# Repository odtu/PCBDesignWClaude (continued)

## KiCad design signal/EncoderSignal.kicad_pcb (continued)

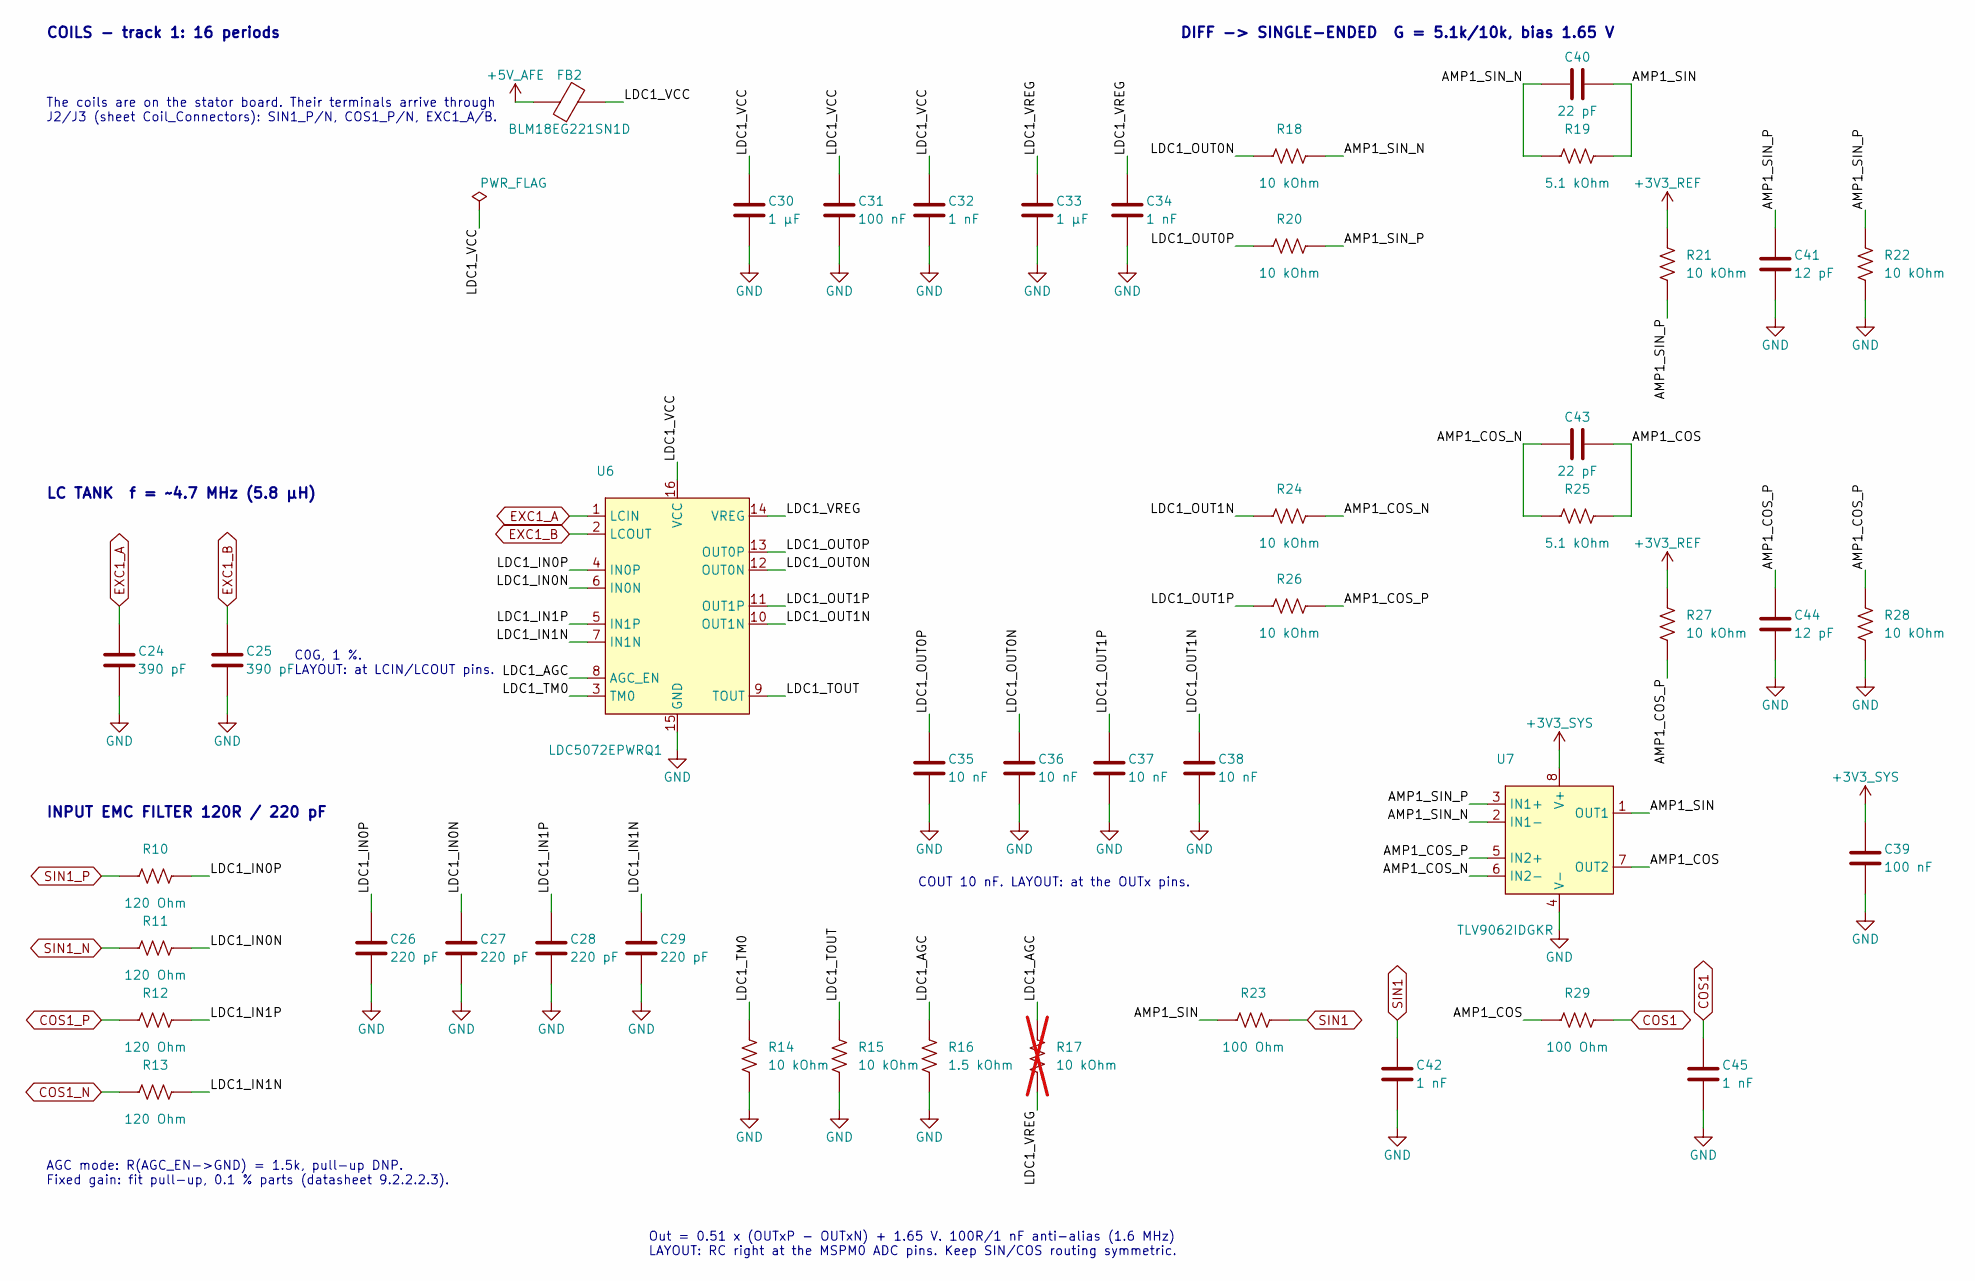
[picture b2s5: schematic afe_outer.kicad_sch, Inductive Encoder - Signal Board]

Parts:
C24, C25: 390 pF; 0603_Medium; Tolerance ±5%; Voltage Rating 50V; Digi-Key Number 490-8006-1-ND
C26, C27, C28, C29: 220 pF; 0603_Medium; Tolerance ±5%; Voltage Rating 50V; Digi-Key Number 1276-1985-1-ND
C30, C33: 1 µF; 0603_Medium; Tolerance ±10%; Voltage Rating 10V; Digi-Key Number 1276-1946-1-ND
C31, C39: 100 nF; 0603_Medium; Tolerance ±10%; Voltage Rating 16V; Digi-Key Number 311-1088-1-ND
C32, C34, C42, C45: 1 nF; 0603_Medium; Tolerance ±5%; Voltage Rating 100V; Digi-Key Number 490-4772-1-ND
C35, C36, C37, C38: 10 nF; 0603_Medium; Tolerance ±10%; Voltage Rating 50V; Digi-Key Number 1276-1009-1-ND
C40, C43: 22 pF; 0603_Medium; Tolerance ±50%; Voltage Rating 50V; Digi-Key Number 1276-2228-1-ND
C41, C44: 12 pF; 0603_Medium; Tolerance ±5%; Voltage Rating 100V; Digi-Key Number 1276-CL10C120JC81PNCCT-ND
FB2: BLM18EG221SN1D; 0603_Medium; Current Rating 2A; Digi-Key Number 490-3992-1-ND
R10, R11, R12, R13: 120 Ohm; 0603_Medium; Tolerance ±1%; Mouser Number 708-RMCF0603FT120R
R14, R15, R18, R20, R21, R22, R24, R26, R27, R28: 10 kOhm; 0603_Medium; Tolerance ±1%; Mouser Number 603-RC0603FR-0710KL
R16: 1.5 kOhm; 0603_Medium; Tolerance ±1%; Mouser Number 708-RMCF0603FT1K50
R17: 10 kOhm; 0603_Medium; Tolerance ±1%; Mouser Number 603-RC0603FR-0710KL; not fitted
R19, R25: 5.1 kOhm; 0603_Medium; Tolerance ±1%; Mouser Number 708-RMCF0603FT5K10
R23, R29: 100 Ohm; 0603_Medium; Tolerance ±1%; Mouser Number 603-RC0603FR-07100RL
U6: LDC5072EPWRQ1; TSSOP-16_PW; Voltage Rating 3.3V, 5V; Digi-Key Number 296-LDC5072EPWRQ1-ND
U7: TLV9062IDGKR; VSSOP-8_DGK; Supply Voltage Range 1.8V up to 5.5V; Digi-Key Number 296-50012-1-ND

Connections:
+3V3_REF: R21.1, R27.1; also elsewhere on the board
+3V3_SYS: C39.1, U7.8 (V+); also elsewhere on the board
+5V_AFE: FB2.1; also elsewhere on the board
/AFE_Outer/AMP1_COS: C43.2, R25.2, R29.1, U7.7 (OUT2)
/AFE_Outer/AMP1_COS_N: C43.1, R24.2, R25.1, U7.6 (IN2-)
/AFE_Outer/AMP1_COS_P: C44.1, R26.2, R27.2, R28.1, U7.5 (IN2+)
/AFE_Outer/AMP1_SIN: C40.2, R19.2, R23.1, U7.1 (OUT1)
/AFE_Outer/AMP1_SIN_N: C40.1, R18.2, R19.1, U7.2 (IN1-)
/AFE_Outer/AMP1_SIN_P: C41.1, R20.2, R21.2, R22.1, U7.3 (IN1+)
/AFE_Outer/LDC1_AGC: R16.1, R17.2, U6.8 (AGC_EN)
/AFE_Outer/LDC1_IN0N: C27.1, R11.2, U6.6 (IN0N)
/AFE_Outer/LDC1_IN0P: C26.1, R10.2, U6.4 (IN0P)
/AFE_Outer/LDC1_IN1N: C29.1, R13.2, U6.7 (IN1N)
/AFE_Outer/LDC1_IN1P: C28.1, R12.2, U6.5 (IN1P)
/AFE_Outer/LDC1_OUT0N: C36.1, R18.1, U6.12 (OUT0N)
/AFE_Outer/LDC1_OUT0P: C35.1, R20.1, U6.13 (OUT0P)
/AFE_Outer/LDC1_OUT1N: C38.1, R24.1, U6.10 (OUT1N)
/AFE_Outer/LDC1_OUT1P: C37.1, R26.1, U6.11 (OUT1P)
/AFE_Outer/LDC1_TM0: R14.1, U6.3 (TM0)
/AFE_Outer/LDC1_TOUT: R15.1, U6.9 (TOUT)
/AFE_Outer/LDC1_VCC: C30.1, C31.1, C32.1, FB2.2, U6.16 (VCC)
/AFE_Outer/LDC1_VREG: C33.1, C34.1, R17.1, U6.14 (VREG)
COS1: C45.1, R29.2; also elsewhere on the board
COS1_N: R13.1; also elsewhere on the board
COS1_P: R12.1; also elsewhere on the board
EXC1_A: C24.1, U6.1 (LCIN); also elsewhere on the board
EXC1_B: C25.1, U6.2 (LCOUT); also elsewhere on the board
GND: C24.2, C25.2, C26.2, C27.2, C28.2, C29.2, C30.2, C31.2, C32.2, C33.2, C34.2, C35.2, C36.2, C37.2, C38.2, C39.2, C41.2, C42.2, C44.2, C45.2, R14.2, R15.2, R16.2, R22.2, R28.2, U6.15 (GND), U7.4 (V-); also elsewhere on the board
SIN1: C42.1, R23.2; also elsewhere on the board
SIN1_N: R11.1; also elsewhere on the board
SIN1_P: R10.1; also elsewhere on the board

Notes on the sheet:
COILS - track 1: 16 periods
The coils are on the stator board. Their terminals arrive through J2/J3 (sheet Coil_Connectors): SIN1_P/N, COS1_P/N, EXC1_A/B.
LC TANK f = ~4.7 MHz (5.8 µH)
C0G, 1 %. LAYOUT: at LCIN/LCOUT pins.
INPUT EMC FILTER 120R / 220 pF
AGC mode: R(AGC_EN->GND) = 1.5k, pull-up DNP. Fixed gain: fit pull-up, 0.1 % parts (datasheet 9.2.2.2.3).
COUT 10 nF. LAYOUT: at the OUTx pins.
DIFF -> SINGLE-ENDED G = 5.1k/10k, bias 1.65 V
Out = 0.51 x (OUTxP - OUTxN) + 1.65 V. 100R/1 nF anti-alias (1.6 MHz) LAYOUT: RC right at the MSPM0 ADC pins. Keep SIN/COS routing symmetric.

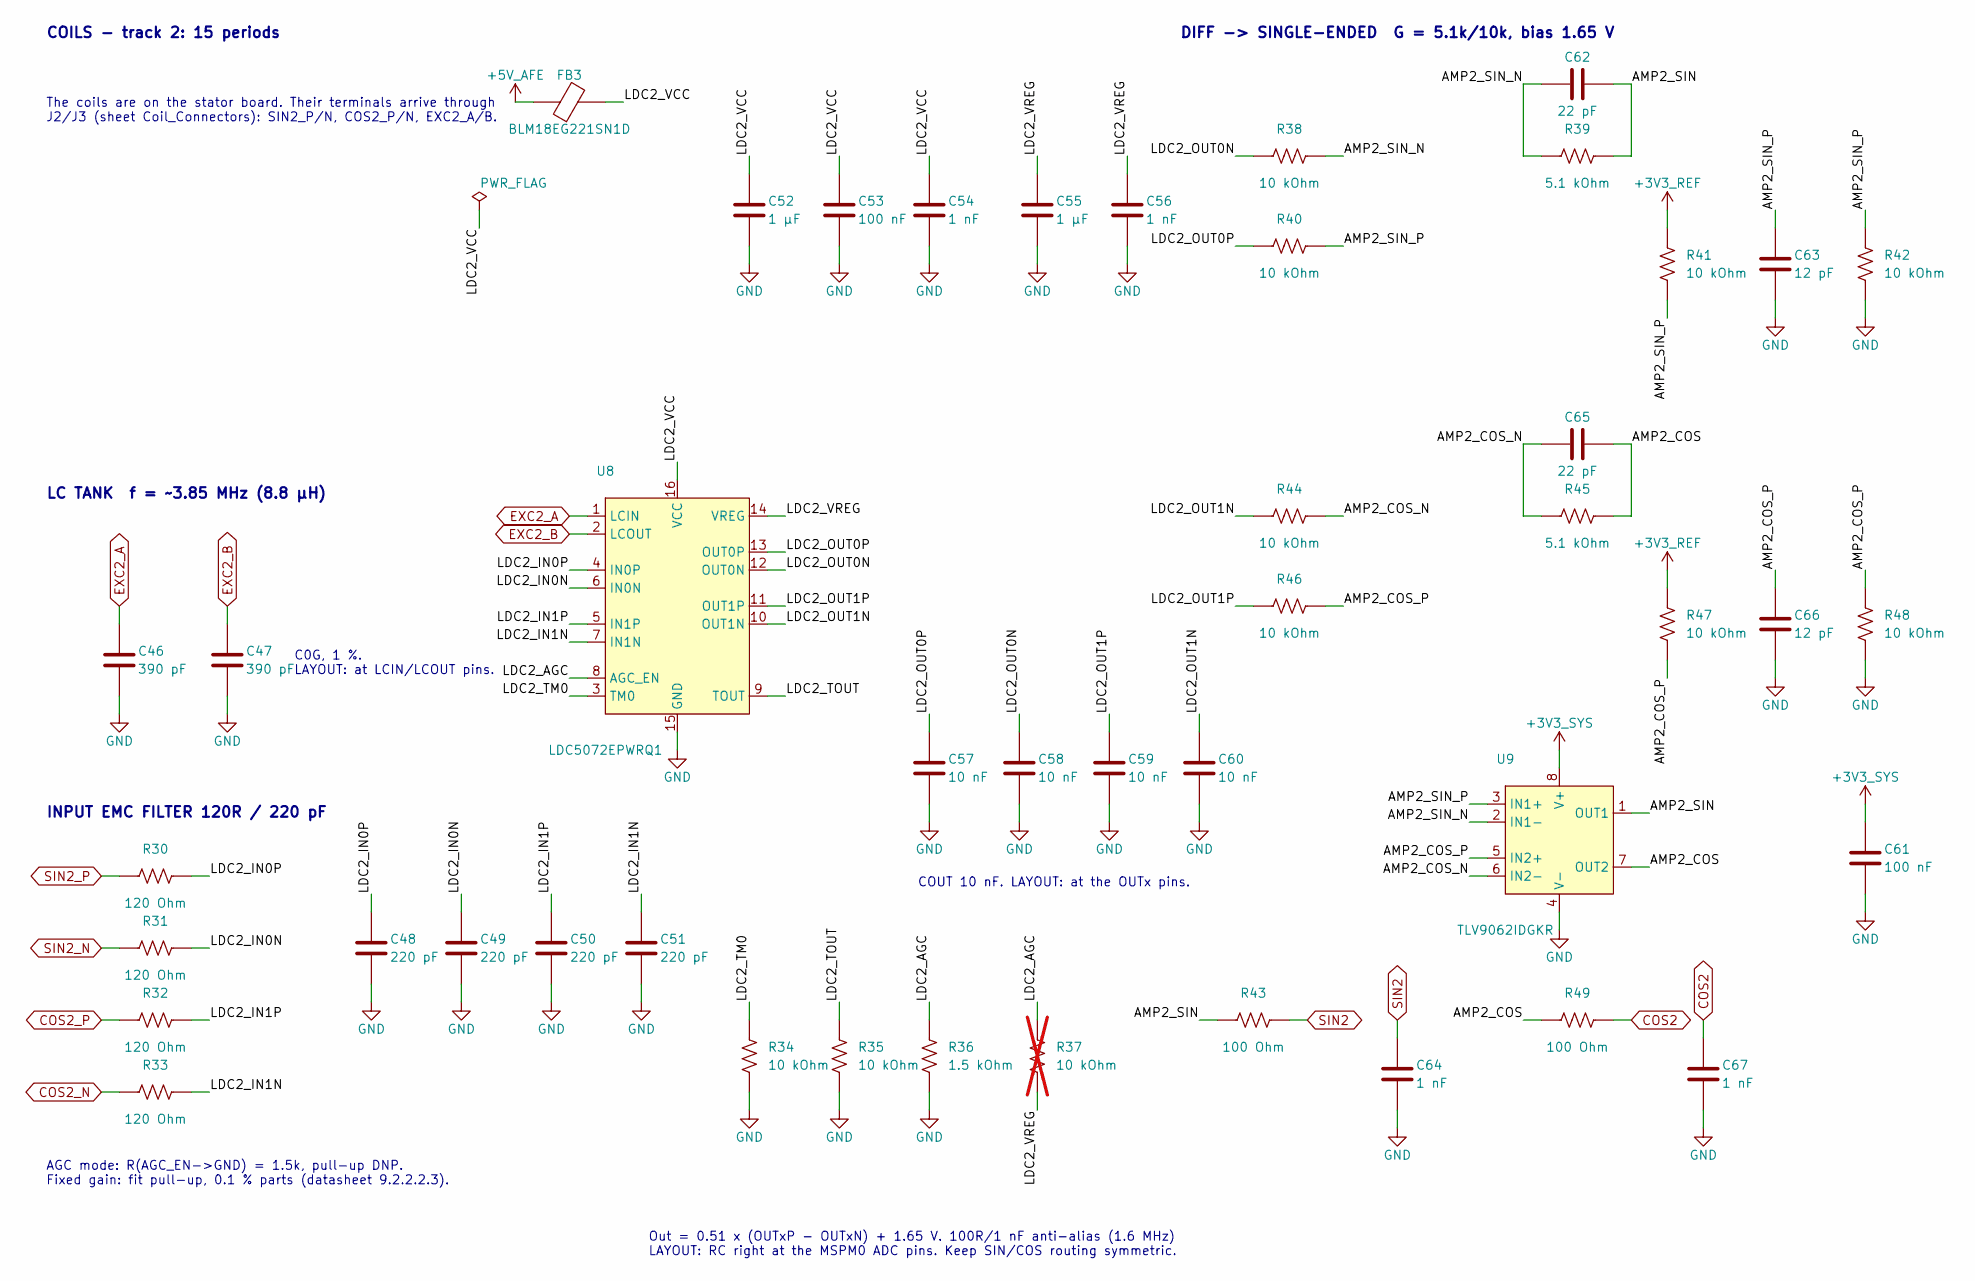
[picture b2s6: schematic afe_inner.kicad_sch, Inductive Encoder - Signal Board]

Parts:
C46, C47: 390 pF; 0603_Medium; Tolerance ±5%; Voltage Rating 50V; Digi-Key Number 490-8006-1-ND
C48, C49, C50, C51: 220 pF; 0603_Medium; Tolerance ±5%; Voltage Rating 50V; Digi-Key Number 1276-1985-1-ND
C52, C55: 1 µF; 0603_Medium; Tolerance ±10%; Voltage Rating 10V; Digi-Key Number 1276-1946-1-ND
C53, C61: 100 nF; 0603_Medium; Tolerance ±10%; Voltage Rating 16V; Digi-Key Number 311-1088-1-ND
C54, C56, C64, C67: 1 nF; 0603_Medium; Tolerance ±5%; Voltage Rating 100V; Digi-Key Number 490-4772-1-ND
C57, C58, C59, C60: 10 nF; 0603_Medium; Tolerance ±10%; Voltage Rating 50V; Digi-Key Number 1276-1009-1-ND
C62, C65: 22 pF; 0603_Medium; Tolerance ±50%; Voltage Rating 50V; Digi-Key Number 1276-2228-1-ND
C63, C66: 12 pF; 0603_Medium; Tolerance ±5%; Voltage Rating 100V; Digi-Key Number 1276-CL10C120JC81PNCCT-ND
FB3: BLM18EG221SN1D; 0603_Medium; Current Rating 2A; Digi-Key Number 490-3992-1-ND
R30, R31, R32, R33: 120 Ohm; 0603_Medium; Tolerance ±1%; Mouser Number 708-RMCF0603FT120R
R34, R35, R38, R40, R41, R42, R44, R46, R47, R48: 10 kOhm; 0603_Medium; Tolerance ±1%; Mouser Number 603-RC0603FR-0710KL
R36: 1.5 kOhm; 0603_Medium; Tolerance ±1%; Mouser Number 708-RMCF0603FT1K50
R37: 10 kOhm; 0603_Medium; Tolerance ±1%; Mouser Number 603-RC0603FR-0710KL; not fitted
R39, R45: 5.1 kOhm; 0603_Medium; Tolerance ±1%; Mouser Number 708-RMCF0603FT5K10
R43, R49: 100 Ohm; 0603_Medium; Tolerance ±1%; Mouser Number 603-RC0603FR-07100RL
U8: LDC5072EPWRQ1; TSSOP-16_PW; Voltage Rating 3.3V, 5V; Digi-Key Number 296-LDC5072EPWRQ1-ND
U9: TLV9062IDGKR; VSSOP-8_DGK; Supply Voltage Range 1.8V up to 5.5V; Digi-Key Number 296-50012-1-ND

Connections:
+3V3_REF: R41.1, R47.1; also elsewhere on the board
+3V3_SYS: C61.1, U9.8 (V+); also elsewhere on the board
+5V_AFE: FB3.1; also elsewhere on the board
/AFE_Inner/AMP2_COS: C65.2, R45.2, R49.1, U9.7 (OUT2)
/AFE_Inner/AMP2_COS_N: C65.1, R44.2, R45.1, U9.6 (IN2-)
/AFE_Inner/AMP2_COS_P: C66.1, R46.2, R47.2, R48.1, U9.5 (IN2+)
/AFE_Inner/AMP2_SIN: C62.2, R39.2, R43.1, U9.1 (OUT1)
/AFE_Inner/AMP2_SIN_N: C62.1, R38.2, R39.1, U9.2 (IN1-)
/AFE_Inner/AMP2_SIN_P: C63.1, R40.2, R41.2, R42.1, U9.3 (IN1+)
/AFE_Inner/LDC2_AGC: R36.1, R37.2, U8.8 (AGC_EN)
/AFE_Inner/LDC2_IN0N: C49.1, R31.2, U8.6 (IN0N)
/AFE_Inner/LDC2_IN0P: C48.1, R30.2, U8.4 (IN0P)
/AFE_Inner/LDC2_IN1N: C51.1, R33.2, U8.7 (IN1N)
/AFE_Inner/LDC2_IN1P: C50.1, R32.2, U8.5 (IN1P)
/AFE_Inner/LDC2_OUT0N: C58.1, R38.1, U8.12 (OUT0N)
/AFE_Inner/LDC2_OUT0P: C57.1, R40.1, U8.13 (OUT0P)
/AFE_Inner/LDC2_OUT1N: C60.1, R44.1, U8.10 (OUT1N)
/AFE_Inner/LDC2_OUT1P: C59.1, R46.1, U8.11 (OUT1P)
/AFE_Inner/LDC2_TM0: R34.1, U8.3 (TM0)
/AFE_Inner/LDC2_TOUT: R35.1, U8.9 (TOUT)
/AFE_Inner/LDC2_VCC: C52.1, C53.1, C54.1, FB3.2, U8.16 (VCC)
/AFE_Inner/LDC2_VREG: C55.1, C56.1, R37.1, U8.14 (VREG)
COS2: C67.1, R49.2; also elsewhere on the board
COS2_N: R33.1; also elsewhere on the board
COS2_P: R32.1; also elsewhere on the board
EXC2_A: C46.1, U8.1 (LCIN); also elsewhere on the board
EXC2_B: C47.1, U8.2 (LCOUT); also elsewhere on the board
GND: C46.2, C47.2, C48.2, C49.2, C50.2, C51.2, C52.2, C53.2, C54.2, C55.2, C56.2, C57.2, C58.2, C59.2, C60.2, C61.2, C63.2, C64.2, C66.2, C67.2, R34.2, R35.2, R36.2, R42.2, R48.2, U8.15 (GND), U9.4 (V-); also elsewhere on the board
SIN2: C64.1, R43.2; also elsewhere on the board
SIN2_N: R31.1; also elsewhere on the board
SIN2_P: R30.1; also elsewhere on the board

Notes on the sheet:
COILS - track 2: 15 periods
The coils are on the stator board. Their terminals arrive through J2/J3 (sheet Coil_Connectors): SIN2_P/N, COS2_P/N, EXC2_A/B.
LC TANK f = ~3.85 MHz (8.8 µH)
C0G, 1 %. LAYOUT: at LCIN/LCOUT pins.
INPUT EMC FILTER 120R / 220 pF
AGC mode: R(AGC_EN->GND) = 1.5k, pull-up DNP. Fixed gain: fit pull-up, 0.1 % parts (datasheet 9.2.2.2.3).
COUT 10 nF. LAYOUT: at the OUTx pins.
DIFF -> SINGLE-ENDED G = 5.1k/10k, bias 1.65 V
Out = 0.51 x (OUTxP - OUTxN) + 1.65 V. 100R/1 nF anti-alias (1.6 MHz) LAYOUT: RC right at the MSPM0 ADC pins. Keep SIN/COS routing symmetric.

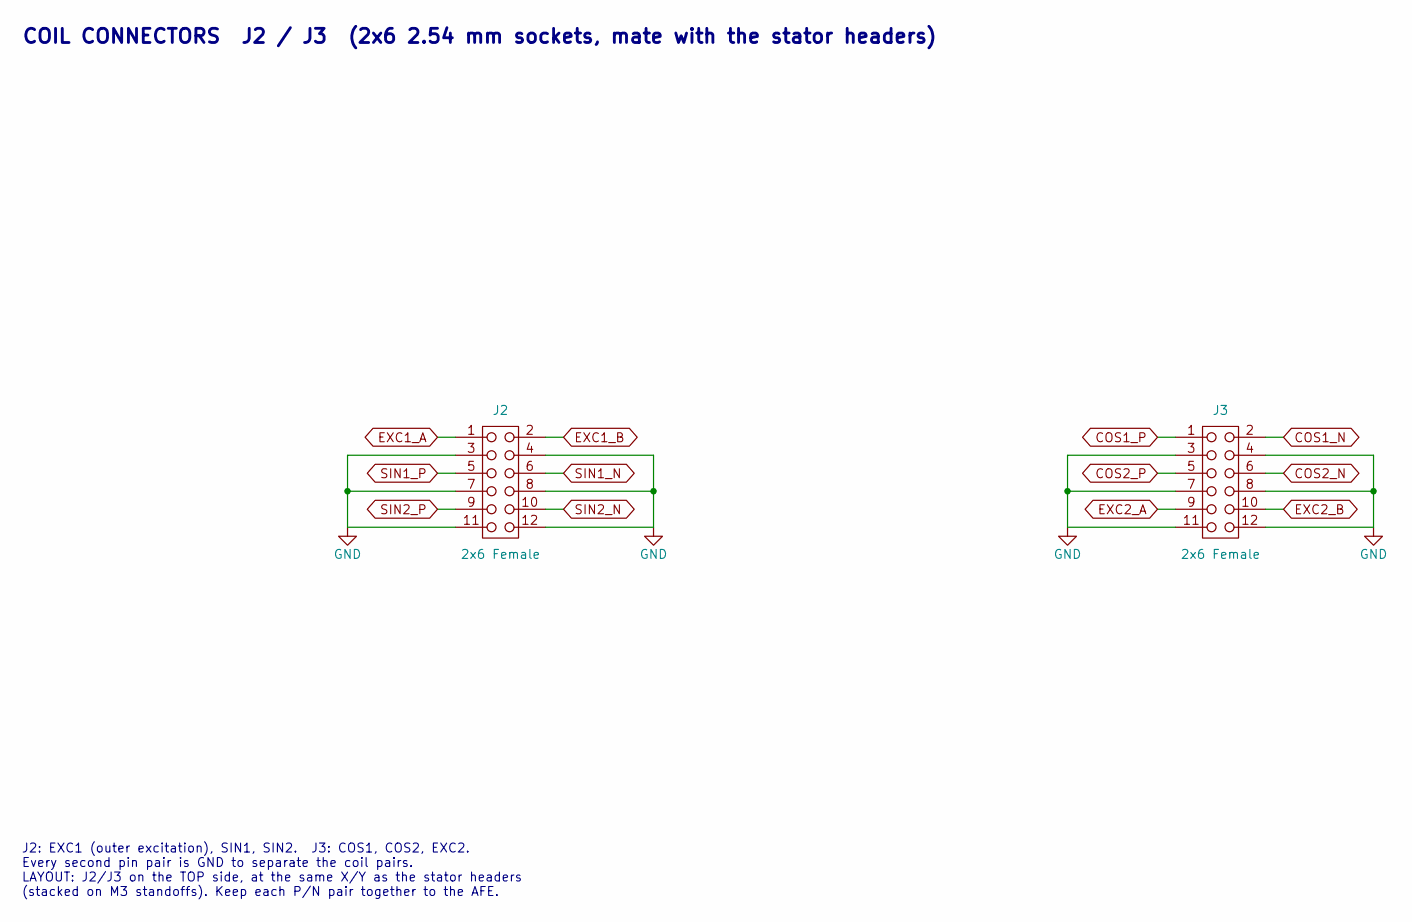
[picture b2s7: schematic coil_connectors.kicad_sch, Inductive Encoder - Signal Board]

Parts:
J2, J3: 2x6 Female; 61301221821; Current Rating 3A; Voltage Rating 250V; Digi-Key Number 732-61301221821-ND

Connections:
COS1_N: J3.2; also elsewhere on the board
COS1_P: J3.1; also elsewhere on the board
COS2_N: J3.6; also elsewhere on the board
COS2_P: J3.5; also elsewhere on the board
EXC1_A: J2.1; also elsewhere on the board
EXC1_B: J2.2; also elsewhere on the board
EXC2_A: J3.9; also elsewhere on the board
EXC2_B: J3.10; also elsewhere on the board
GND: J2.3, J2.4, J2.7, J2.8, J2.11, J2.12, J3.3, J3.4, J3.7, J3.8, J3.11, J3.12; also elsewhere on the board
SIN1_N: J2.6; also elsewhere on the board
SIN1_P: J2.5; also elsewhere on the board
SIN2_N: J2.10; also elsewhere on the board
SIN2_P: J2.9; also elsewhere on the board

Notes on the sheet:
COIL CONNECTORS J2 / J3 (2x6 2.54 mm sockets, mate with the stator headers)
J2: EXC1 (outer excitation), SIN1, SIN2. J3: COS1, COS2, EXC2. Every second pin pair is GND to separate the coil pairs. LAYOUT: J2/J3 on the TOP side, at the same X/Y as the stator headers (stacked on M3 standoffs). Keep each P/N pair together to the AFE.

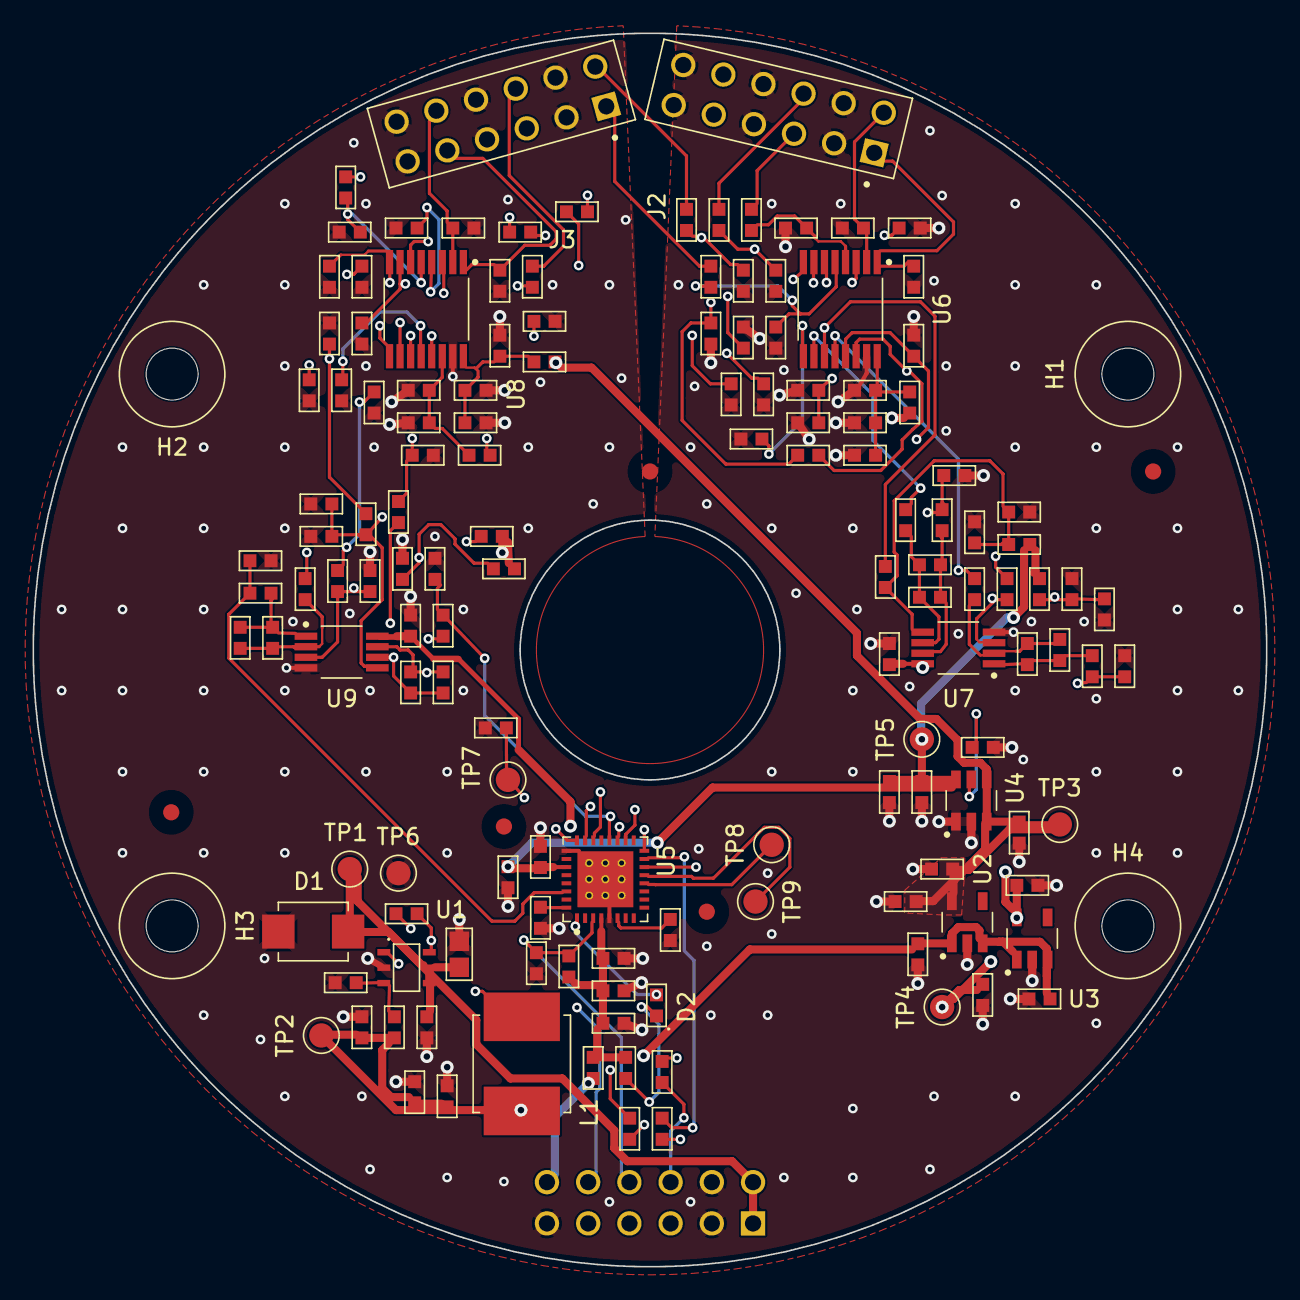
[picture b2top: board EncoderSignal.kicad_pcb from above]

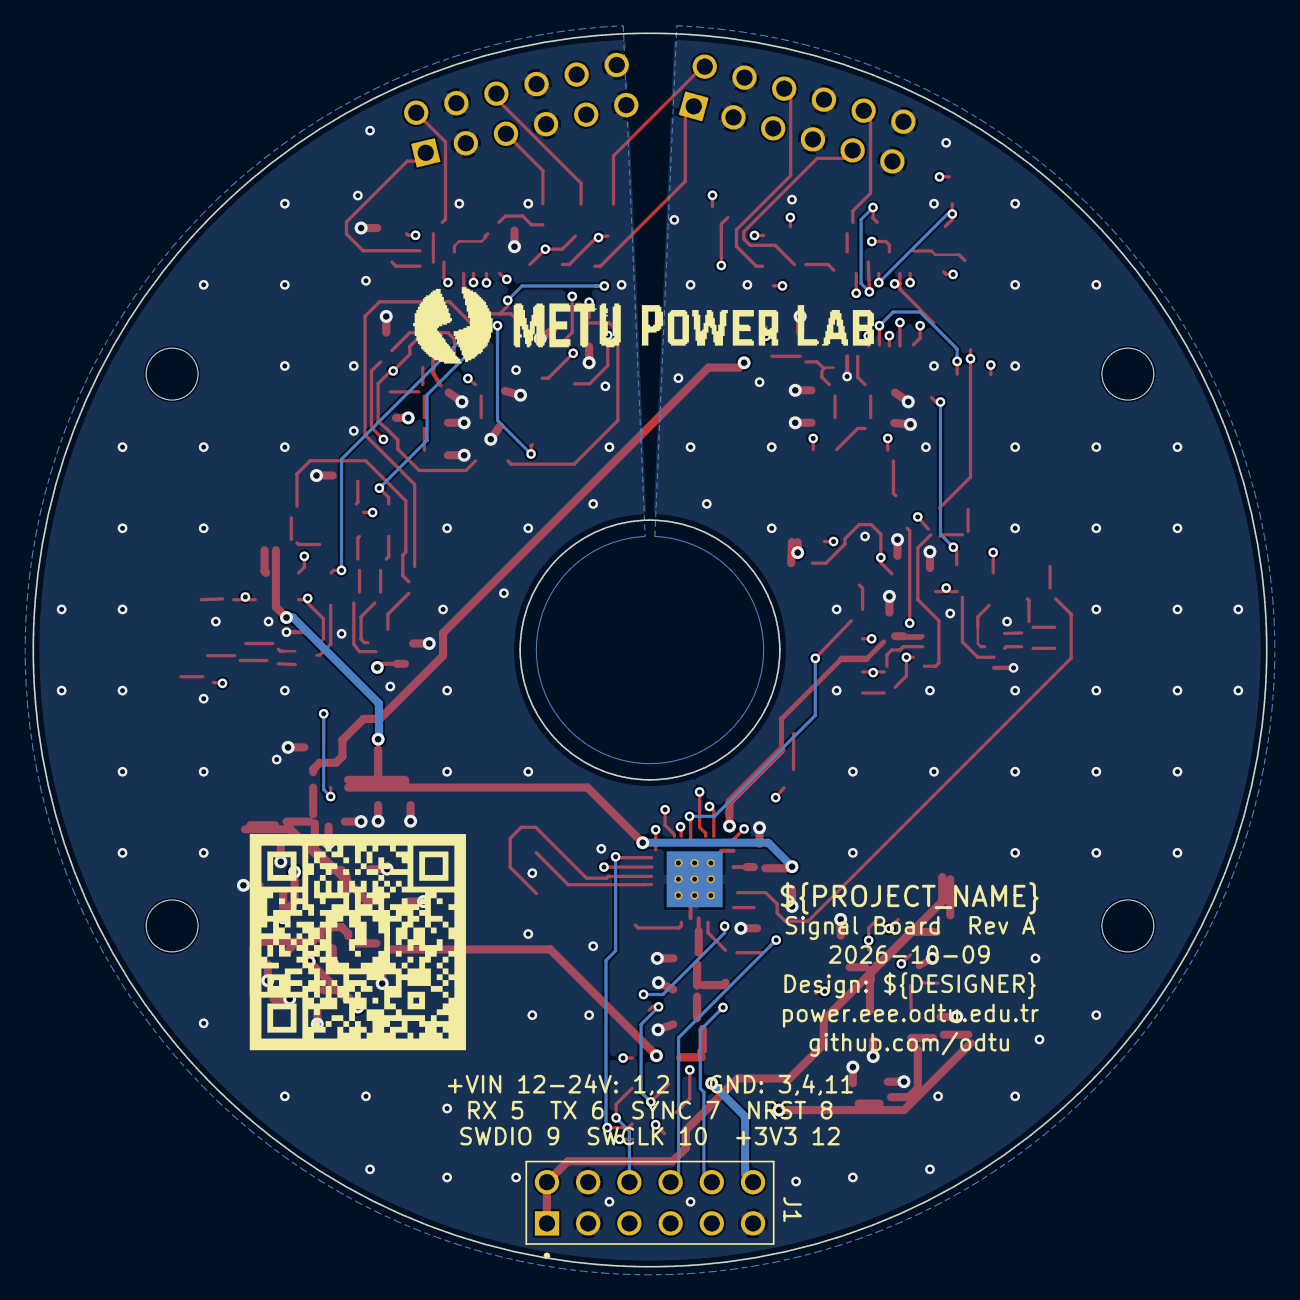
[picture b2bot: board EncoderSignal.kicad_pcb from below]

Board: 4 copper layers, 76.0 x 76.0 mm, 154 parts (3 on the bottom side), 81 nets.

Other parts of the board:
FID1, FID2, FID3, FID4, FID5: Fiducial_1mm_Mask2mm
G1: METUPowerLab_Logo_30mm
G2: METUPowerLab_QRCode_13.3mm
H1, H2, H3, H4: M3_NPTH

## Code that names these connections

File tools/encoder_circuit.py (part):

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R(I, "22 Ohm", (60, 70), "J_UART_RX", "UART_RX")
R(I, "22 Ohm", (60, 85), "UART_TX", "J_UART_TX")
R(I, "22 Ohm", (60, 100), "J_SYNC", "SYNC")
I.text("Pinout\n 1,2  +VIN 12-24 V        3,4,11  GND\n 5  UART_RX (host -> encoder)   6  UART_TX (encoder -> host)\n"
       " 7  SYNC (sample trigger in)     8  NRST\n 9  SWDIO   10  SWCLK   12  +3V3 (debugger VTref, out)\n"
       "UART: 2.5 Mbaud, 8N1 (TIDA-010961 protocol). The MSPM0 ROM bootloader\n"
       "also uses UART0 (PA10/PA11): hold BSL (PA18) high at reset to flash over J1.",
       (30, 130))
I.text("LAYOUT: J1 on the bottom side (away from the target), at the board edge.", (30, 175))

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M.part(ref("U"), *SYM["MSPM0"], (140, 100), 0, pstub={"25": 15.24, "27": 5.08, "4": 15.24}, pins={
    "4": "+3V3_MCU", "5": "GND", "32": "VCORE", "3": "NRST", "6": "ROSC",
    "27": "+3V3_REF", "25": "GND",                     # VREF+ / VREF-
    # SIN1 on A0_12/PA14 (pin 18, next to COS1): the outer AFE is on the right side of
    # the board; A0_0/PA27 (pin 31) sat on the far side of the MCU
    "18": "SIN1", "19": "COS1", "30": "SIN2", "20": "COS2",   # A0_12 / A1_0 / A0_1 / A1_1
    "14": "UART_TX", "15": "UART_RX", "16": "SYNC", "23": "SWDIO", "24": "SWCLK",
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TP(M, "TEST_B", (245, 60))
M.part("#FLG04", "METUPowerLab_Schematic_PowerSymbols", "PWR_FLAG", (65, 80), 180, {"1": "+3V3_MCU"})
M.text("ADC: SIN on ADC0, COS on ADC1 of the same track -> sampled simultaneously.\n"
       "SIN1 A0_12/PA14, COS1 A1_0/PA15, SIN2 A0_1/PA26, COS2 A1_1/PA16.\n"
       "VREF+ = REF35330 (3.3 V), VREF- = GND. ROSC 100k 0.1 % for SYSOSC FCL.\n"
       "LAYOUT: decoupling caps at VDD/VSS and VCORE pins, VREF caps at PA23.\n"
       "LAYOUT: ROSC resistor right at PA2, short ground return.", (160, 150))

# ---------------------------------------------------------------------------
# Sheets 5/6: AFE (one per track)
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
